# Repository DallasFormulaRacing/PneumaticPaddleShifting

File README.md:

# PneumaticPaddleShifting

## Table of Contents
1. [Objective](#objective)
2. [Hardware and Equipment](#hardware-and-equipment)
3. [Firmware Tech Stack](#firmware-tech-stack)
4. [Automation](#automation)
5. [Design](#design)

## Objective:
- Optimize the user's response to a down-shift and up-shift command.
- Maintain strict practices and edge cases for critical safety.
- Build the first fully-fledged DAQ with re-usable code through:
    - The Layered Architecture design pattern
    - Modularity of components
    - Hardware abstraction

## Hardware and Equipment
### Target Device
The [STM32 Nucleo F466RE](https://www.st.com/en/evaluation-tools/nucleo-f446re.html) microcontroller development board is used as the current target device for code merged to the `main` and `develop` branches. Theoretically, other Arm Cortex M4 based STM32 devices with the necessary peripherals should be able to run the same program.

## Firmware Tech Stack
- STM32 Hardware Abstraction Layer ([HAL](https://www.st.com/resource/en/user_manual/um1725-description-of-stm32f4-hal-and-lowlayer-drivers-stmicroelectronics.pdf))
  - Generated by STM32CubeMX within the CubeIDE environment, which also provides the `arm-none-eabi` toolchain.
  - Serves as a set of drivers or a Board Support Package (BSP) to interface with the microcontroller.

## Automation
- Unit tests are developed using [Google Test](https://google.github.io/googletest/) and are maintained in `Shifter_System/Tests`.
- See our [Unit Testing page](https://github.com/DallasFormulaRacing/DataAcquisition2.0/wiki/Unit-Testing) for running them locally by leveraging [Docker](https://docs.docker.com/get-started/overview/).
- Continuous Integration (CI)
  - The firmware is compiled as an stm32CubeIDE project using the following GitHub Action: [xanderhendriks/action-build-stm32cubeide](https://github.com/marketplace/actions/build-stm32cubeide-project).
  - The unit tests are compiled and ran using [CMake](https://cmake.org/cmake/help/latest/index.html) with [Ninja](https://ninja-build.org/manual.html). 

## Design

High level system diagram:

Firmware design:

### User Input

It is assumed that the user inputs are simple GPIO signals (i.e., high and low voltages). The upshift and downshift paddle will request their respective shift. The neutral button is for the user to set the car into neutral, and this may be verified with a neutral “monitor”. The neutral monitor is to act as some sort of sensor or switch.  

Do note, however, that these inputs have not yet been tested. It is currently unknown whether they will require any signal “debouncing” so that the behavior is not jittery or sporadic. It has also been highly recommended to consider more fail-safe mechanisms for the scenario that the user input begins to malfunction. 

### Reading ECU Data

The device reads RPM, TPS, and wheel speeds from the PE3 8400-P ECU. This ECU implementation library was adopted from the race team’s previous efforts in other projects. 

### Shift Controller

The Shift Controller is a high-level component responsible for evaluating the driver’s shift requests. It depends on an ECU and several GPIO components to be used. Internally, a state machine is used to perform different behaviors. This approach offers the following advantages: dramatically simplifies the logic, increases performance, isolated behavior, and transition actions. The performance is increased as it only performs the conditional checks that are unique to each state. Due to the isolated behaviors, we can also easily determine and rigorously test every edge case for every state.

You may see the design of the state machine below in Figure 9. In practice, there are 6 gears. However, gears 2 through 5 had the same logic and state transition conditions, so they were condensed into a single state. So, the nomenclature was established as the following: Low Gear refers to first gear, Mid Gears refers to second to fifth gear, and High Gear refers to sixth gear. 

One important design choice is how we intended to manage the transition to/from the neutral state. In practice, to go from first to second gear, the driver typically needs to go through neutral. Although an “immediate pass-through" transition was considered, the team ultimately decided to require the driver to manually transition through neutral. This user experience will be in reminiscence of a typical vehicle to offer a more seamless and practical learning curve to use. 

It is worth mentioning that, due to time constraints in the development of the Shift Actuation, the Shift Controller is incomplete in respect to commanding for a shift. 

`ShiftController` state machine:

### Shift Actuation

It is assumed that the required hardware interface for the shift actuator would be a GPIO (i.e., high and low) signal. However, due to time constraints, requirements of the hardware interface were not tested and verified for modifications.

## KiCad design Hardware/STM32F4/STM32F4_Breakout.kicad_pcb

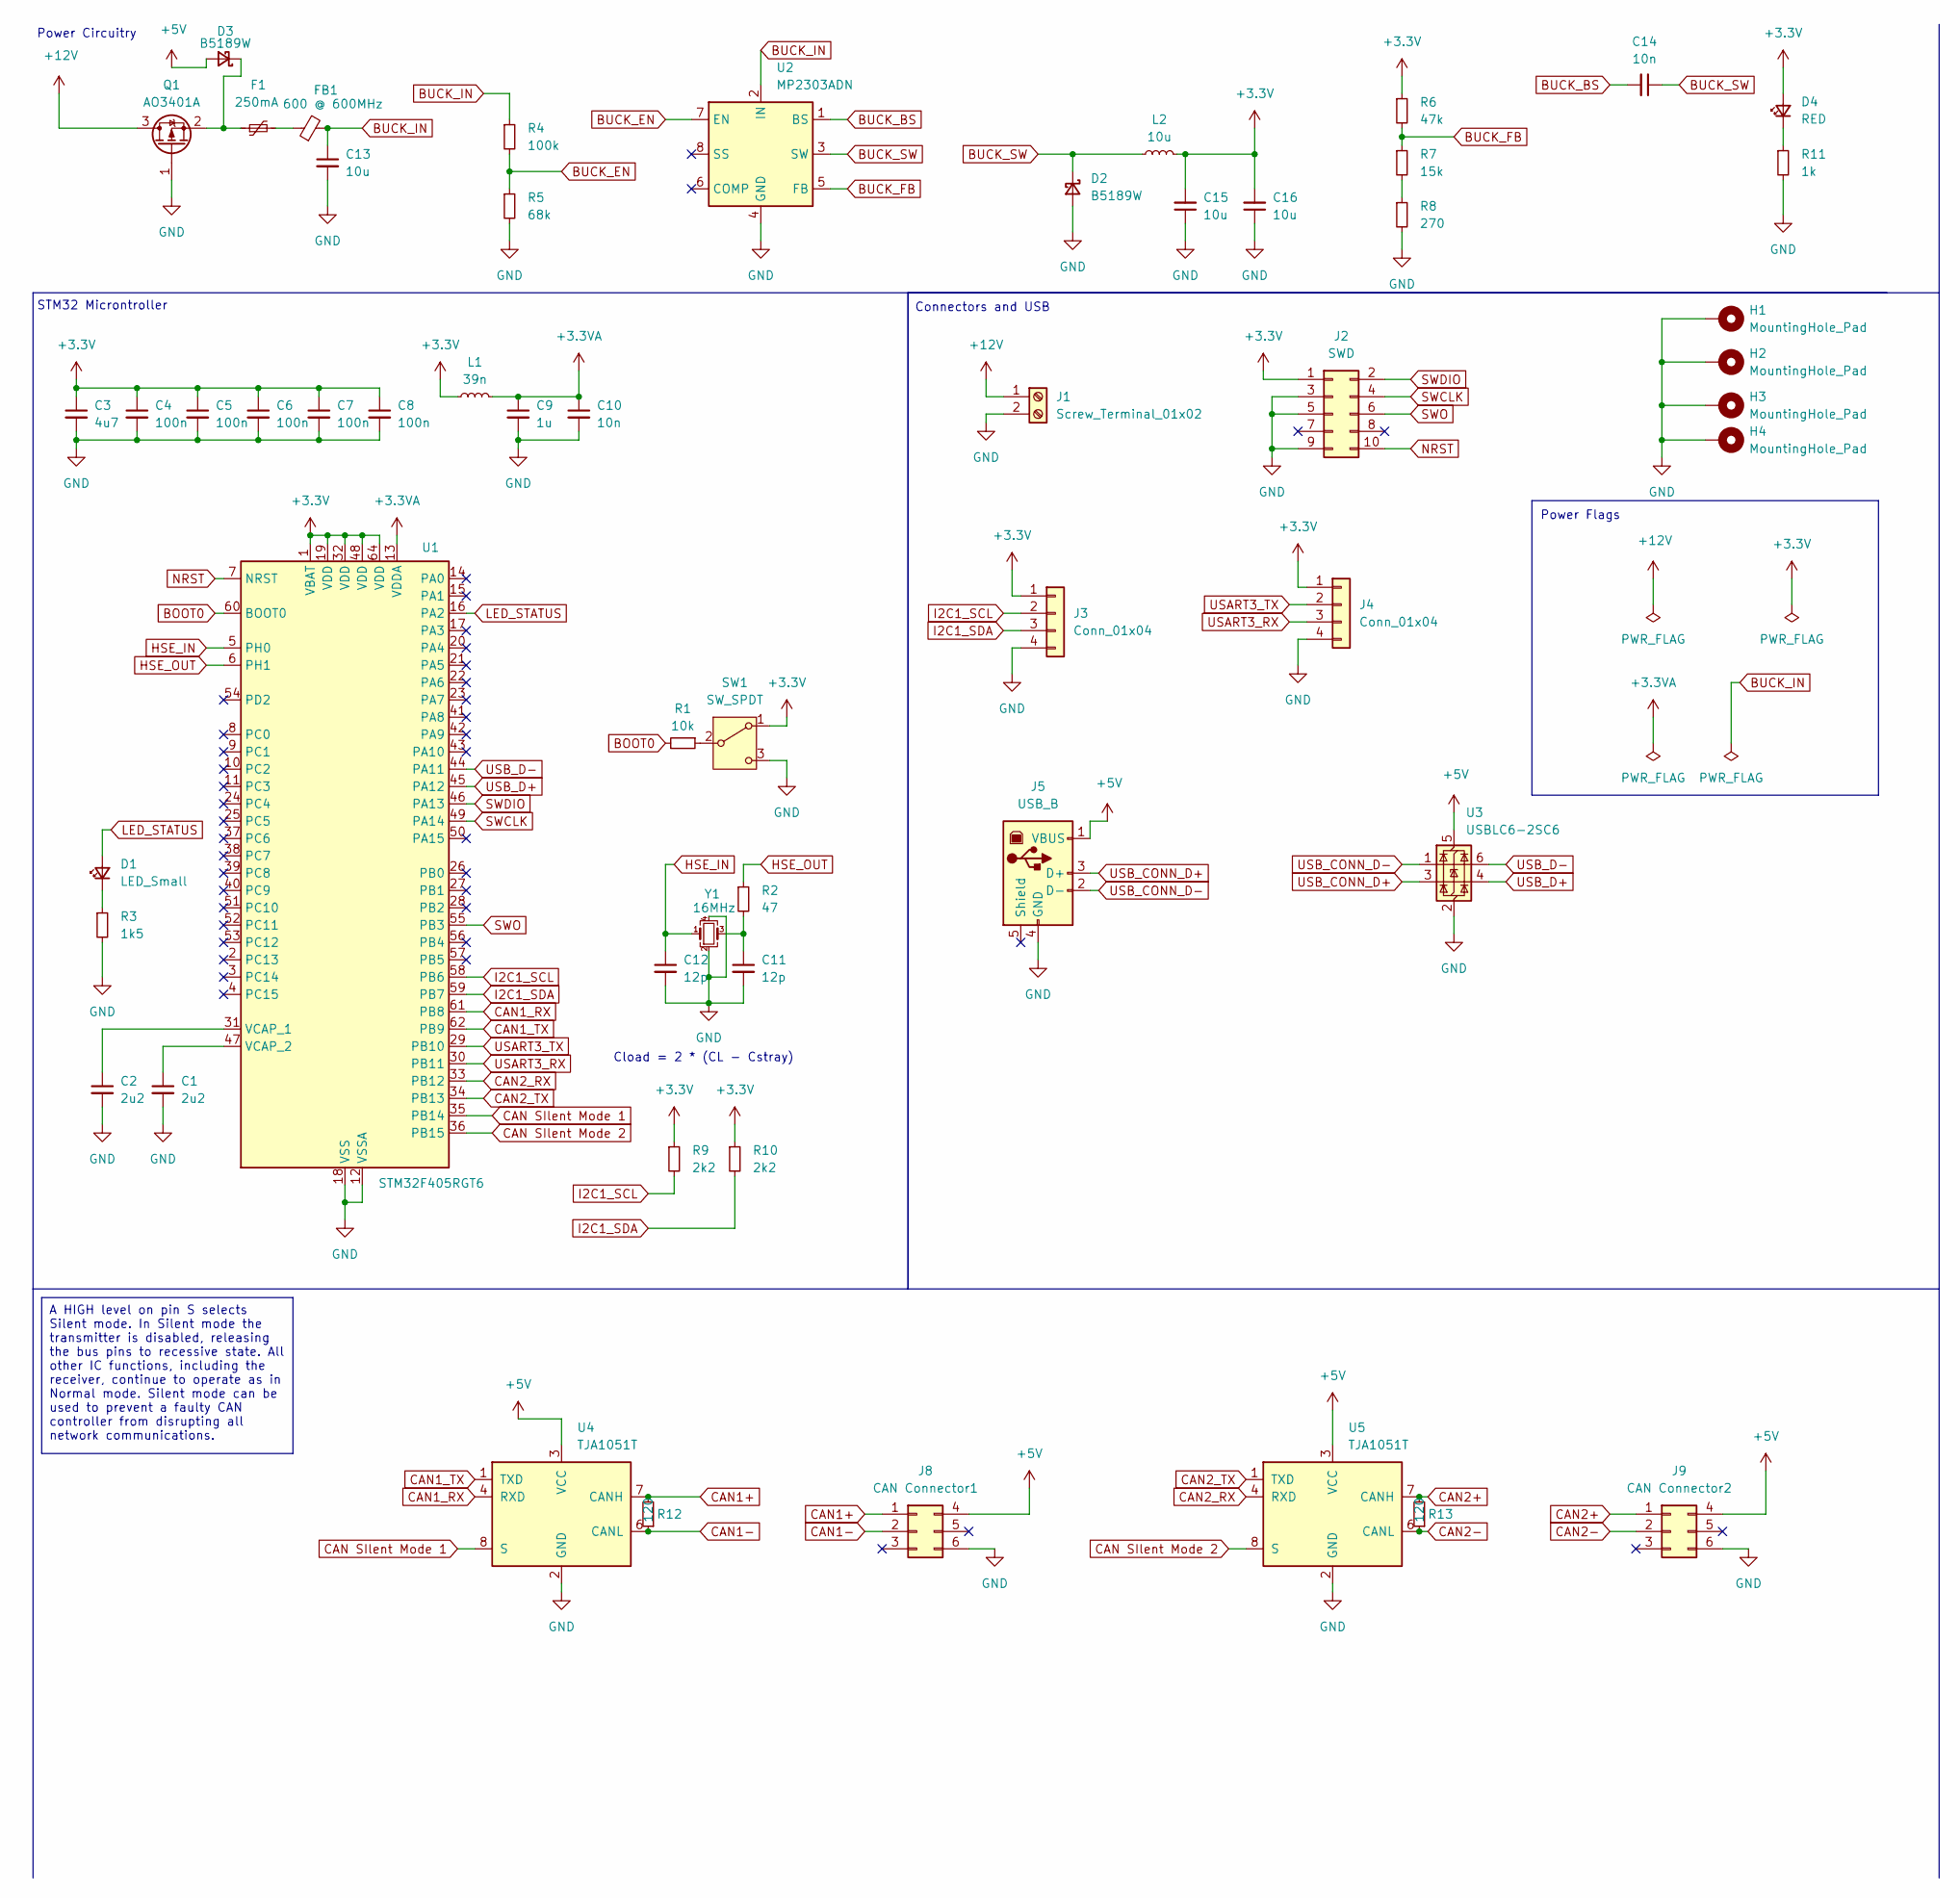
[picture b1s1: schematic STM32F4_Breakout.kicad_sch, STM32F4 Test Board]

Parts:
C1, C2: 2u2; C_0603_1608Metric
C3: 4u7; C_0603_1608Metric
C4, C5, C6, C7, C8: 100n; C_0402_1005Metric
C9: 1u; C_0402_1005Metric
C10: 10n; C_0402_1005Metric
C11, C12: 12p; C_0402_1005Metric
C13, C15, C16: 10u; C_1206_3216Metric
C14: 10n; C_0603_1608Metric
D1: LED_Small; LED_0603_1608Metric
D2, D3: B5189W; D_SOD-123
D4: RED; LED_0603_1608Metric
F1: 250mA; Fuse_1206_3216Metric
FB1: 600 @ 600MHz; L_0805_2012Metric
H1, H2, H3, H4: MountingHole_Pad; MountingHole_4.3mm_M4_Pad_Via
J1: Screw_Terminal_01x02; TerminalBlock_Phoenix_PT-1,5-2-3.5-H_1x02_P3.50mm_Horizontal
J2: SWD; PinHeader_2x05_P1.27mm_Vertical_SMD
J3, J4: Conn_01x04; Molex_PicoBlade_53048-0410_1x04_P1.25mm_Horizontal
J5: USB_B; USB_B_Lumberg_2411_02_Horizontal
J8: CAN Connector1; Molex_Mega-Fit_76829-0006_2x03_P5.70mm_Vertical
J9: CAN Connector2; Molex_Mega-Fit_76829-0006_2x03_P5.70mm_Vertical
L1: 39n; L_0402_1005Metric
L2: 10u; L_Sunlord_MWSA0518S
Q1: AO3401A; SOT-23
R1: 10k; R_0402_1005Metric
R2: 47; R_0402_1005Metric
R3: 1k5; R_0603_1608Metric
R4: 100k; R_0603_1608Metric
R5: 68k; R_0603_1608Metric
R6: 47k; R_0603_1608Metric
R7: 15k; R_0603_1608Metric
R8: 270; R_0603_1608Metric
R9, R10: 2k2; R_0402_1005Metric
R11: 1k; R_0603_1608Metric
R12, R13: 120; R_0603_1608Metric_Pad0.98x0.95mm_HandSolder; JLCpart# C2906988
SW1: SW_SPDT; SW_SPDT_PCM12
U1: STM32F405RGT6; LQFP-64_10x10mm_P0.5mm
U2: MP2303ADN; SOIC-8-1EP_3.9x4.9mm_P1.27mm_EP2.62x3.51mm
U3: USBLC6-2SC6; SOT-23-6
U4, U5: TJA1051T; SOIC-8_3.9x4.9mm_P1.27mm; JLCpart# C38695
Y1: 16MHz; Crystal_SMD_3225-4Pin_3.2x2.5mm

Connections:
+3.3V: C3.1, C4.1, C5.1, C6.1, C7.1, C8.1, C15.2, C16.2, D4.2 (A), J2.1, J3.1, J4.1, L1.1, L2.2, R6.1, R9.1, R10.1, SW1.1 (A), U1.1 (VBAT), U1.19 (VDD), U1.32 (VDD), U1.48 (VDD), U1.64 (VDD)
+3.3VA: C9.1, C10.1, L1.2, U1.13 (VDDA)
+5V: D3.2 (A), J5.1 (VBUS), J8.4, J9.4, U3.5 (VBUS), U4.3 (VCC), U5.3 (VCC)
+12V: J1.1, Q1.3 (D)
BOOT0: R1.2, U1.60 (BOOT0)
BUCK_BS: C14.2, U2.1 (BS)
BUCK_EN: R4.2, R5.1, U2.7 (EN)
BUCK_FB: R6.2, R7.1, U2.5 (FB)
BUCK_IN: C13.1, FB1.2, R4.1, U2.2 (IN)
BUCK_SW: C14.1, D2.1 (K), L2.1, U2.3 (SW)
CAN1+: J8.1, R12.2, U4.7 (CANH)
CAN1-: J8.2, R12.1, U4.6 (CANL)
CAN1_RX: U1.61 (PB8), U4.4 (RXD)
CAN1_TX: U1.62 (PB9), U4.1 (TXD)
CAN2+: J9.1, R13.2, U5.7 (CANH)
CAN2-: J9.2, R13.1, U5.6 (CANL)
CAN2_RX: U1.33 (PB12), U5.4 (RXD)
CAN2_TX: U1.34 (PB13), U5.1 (TXD)
CAN SIlent Mode 1: U1.35 (PB14), U4.8 (S)
CAN SIlent Mode 2: U1.36 (PB15), U5.8 (S)
GND: C1.2, C2.2, C3.2, C4.2, C5.2, C6.2, C7.2, C8.2, C9.2, C10.2, C11.2, C12.2, C13.2, C15.1, C16.1, D2.2 (A), H1.1, H2.1, H3.1, H4.1, J1.2, J2.3, J2.5, J2.9, J3.4, J4.4, J5.4 (GND), J8.6, J9.6, Q1.1 (G), R3.2, R5.2, R8.2, R11.2, SW1.3 (C), U1.12 (VSSA), U1.18 (VSS), U1.63 (VSS), U2.4 (GND), U3.2 (GND), U4.2 (GND), U5.2 (GND), Y1.2, Y1.4
HSE_IN: C12.1, U1.5 (PH0), Y1.1
HSE_OUT: R2.1, U1.6 (PH1)
I2C1_SCL: J3.2, R9.2, U1.58 (PB6)
I2C1_SDA: J3.3, R10.2, U1.59 (PB7)
LED_STATUS: D1.2 (A), U1.16 (PA2)
NRST: J2.10, U1.7 (NRST)
unnamed: C11.1, R2.2, Y1.3
unnamed: D1.1 (K), R3.1
unnamed: D3.1 (K), F1.1, Q1.2 (S)
unnamed: D4.1 (K), R11.1
unnamed: F1.2, FB1.1
unnamed: R7.2, R8.1
unnamed: R1.1, SW1.2 (B)
unnamed: C2.1, U1.31 (VCAP_1)
unnamed: C1.1, U1.47 (VCAP_2)
SWCLK: J2.4, U1.49 (PA14)
SWDIO: J2.2, U1.46 (PA13)
SWO: J2.6, U1.55 (PB3)
USART3_RX: J4.3, U1.30 (PB11)
USART3_TX: J4.2, U1.29 (PB10)
USB_CONN_D+: J5.3 (D+), U3.3 (I/O2)
USB_CONN_D-: J5.2 (D-), U3.1 (I/O1)
USB_D+: U1.45 (PA12), U3.4 (I/O2)
USB_D-: U1.44 (PA11), U3.6 (I/O1)

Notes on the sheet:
A HIGH level on pin S selects Silent mode. In Silent mode the transmitter is disabled, releasing the bus pins to recessive state. All other IC functions, including the receiver, continue to operate as in Normal mode. Silent mode can be used to prevent a faulty CAN controller from disrupting all net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
STM32 Microntroller
Power Flags
Connectors and USB
Power Circuitry
Cload = 2 * (CL - Cstray)

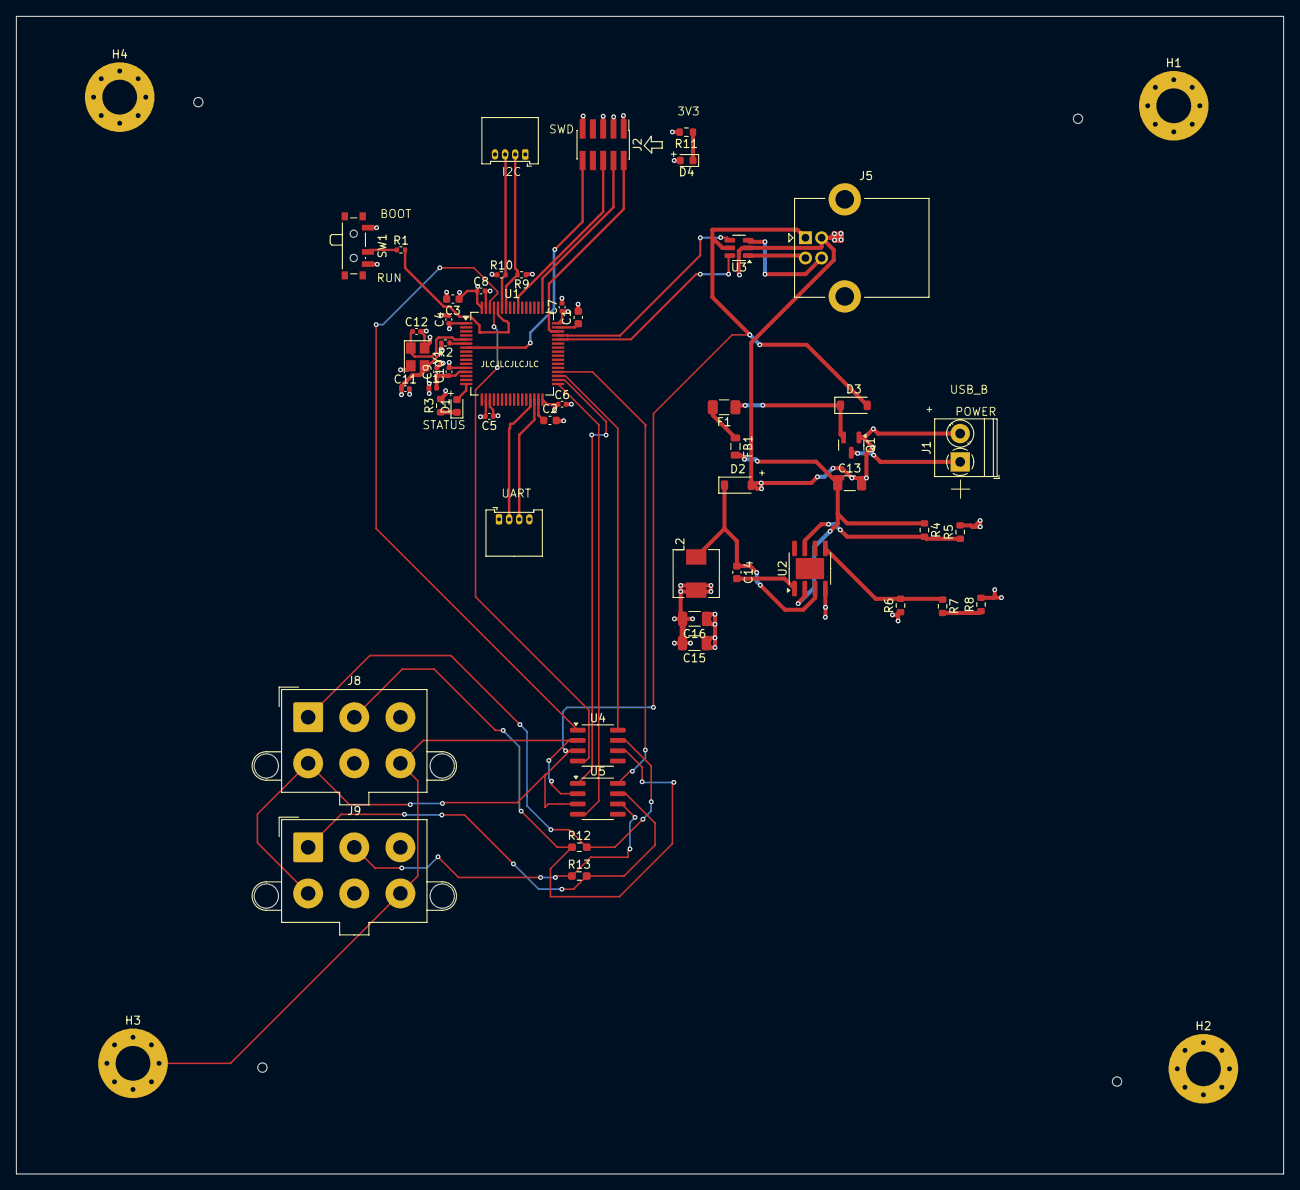
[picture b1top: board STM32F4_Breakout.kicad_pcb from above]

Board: 4 copper layers, 156.6 x 143.1 mm, 56 parts (0 on the bottom side), 45 nets.

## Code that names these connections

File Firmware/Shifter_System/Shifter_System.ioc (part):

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Mcu.Name=STM32F446R(C-E)Tx
Mcu.Package=LQFP64
Mcu.UserName=STM32F446RETx
PA11.Mode=CAN_Activate
PA11.Signal=CAN1_RX
PA12.Mode=CAN_Activate
PA12.Signal=CAN1_TX
PA13.GPIOParameters=GPIO_Label
PA13.GPIO_Label=TMS
PA13.Mode=Serial_Wire
PA13.Signal=SYS_JTMS-SWDIO
PA14.GPIOParameters=GPIO_Label
PA14.GPIO_Label=TCK
PA14.Mode=Serial_Wire
PA14.Signal=SYS_JTCK-SWCLK
PA2.GPIOParameters=GPIO_Label
PA2.GPIO_Label=USART_TX
PA2.Mode=Asynchronous
PA2.Signal=USART2_TX
PA3.GPIOParameters=GPIO_Label
PA3.GPIO_Label=USART_RX
PA3.Mode=Asynchronous
PA3.Signal=USART2_RX
PA5.GPIOParameters=GPIO_Label
PA5.GPIO_Label=LD2 [Green Led]
PA5.Signal=GPIO_Output
PB3.GPIOParameters=GPIO_Label
PB3.GPIO_Label=SWO
PB3.Signal=SYS_JTDO-SWO
PC13.GPIOParameters=GPIO_Label,GPIO_ModeDefaultEXTI
PC13.GPIO_Label=B1 [Blue PushButton]
PC13.GPIO_ModeDefaultEXTI=GPIO_MODE_IT_FALLING
PC13.Signal=GPXTI13
PC14-OSC32_IN.Mode=LSE-External-Oscillator
PC14-OSC32_IN.Signal=RCC_OSC32_IN
PC15-OSC32_OUT.Mode=LSE-External-Oscillator
PC15-OSC32_OUT.Signal=RCC_OSC32_OUT
PH0-OSC_IN.Mode=HSE-External-Oscillator
PH0-OSC_IN.Signal=RCC_OSC_IN
PH1-OSC_OUT.Mode=HSE-External-Oscillator
PH1-OSC_OUT.Signal=RCC_OSC_OUT
RCC.HSE_VALUE=8000000
RCC.SYSCLKFreq_VALUE=84000000
RCC.SYSCLKSource=RCC_SYSCLKSOURCE_PLLCLK
board=NUCLEO-F446RE
boardIOC=true

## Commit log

2024-03-19 Prepared the unit testing environment
2024-04-06 Create shiftCode
    Code responsible for shifting gears.
2024-04-10 Adrian's first PCB revision
2024-04-22 Consolidated Kicad projects
2024-06-14 Created CubeIDE project
2024-06-14 Enabled C++. Added Blinky LED
2024-06-14 Enabled printf()
2024-06-14 Added YAML file for CI build
2024-06-22 ShiftController state machine boilerplate
2024-06-27 First set of ShiftController unit tests
2024-06-27 Updated unit testing workflow target directory
2024-06-28 CAN transceiver
2024-07-09 Porting ECU/CAN library
2024-07-11 RPM and Wheel speed reading
2024-07-11 Integrated rpm and wheel speed into ShiftController
2024-07-11 Updated unit testing fixture to add rpm and wheel speed dependencies
2024-07-12 Added neutral switch gpio to ShiftController constructor
2024-07-12 Added first IGpio mock object to ShiftController tests
2024-07-13 First draft of shifting conditions. More GPIOs added to ShiftController. TPS reading.
2024-07-14 Defined empty test cases. Edge cases for ignoring shift requests at NeutralState and HighGearState. Removed re-usable upshift conditions from unique NeutralState transition
2024-07-22 Update shift_controller_tests.cpp
    Updated upshift conditions
2024-07-24 Update shift_controller_tests.cpp
    Updated the down shift test conditions.
2024-07-24 Update shift_controller_tests.cpp
    Updated Midgear State Cases
2024-07-24 Update shift_controller_tests.cpp
    Updated High gear State cases
2024-07-27 Removed non-existent function call. Re-added GTEST_SKIP notes for test cases lacking complete implementations
